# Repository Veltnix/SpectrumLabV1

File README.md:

<h1 align="center">SpectrumLab V1</h1>

<p align="center">
<b>A Compact VIS–NIR Spectroscopy Development Board powered by ESP32-C3 and AS7263</b>
</p>

<hr>

<h2>📌 Overview</h2>

<p>
<b>SpectrumLab V1</b> is a compact VIS–NIR spectroscopy development board built around the ESP32-C3 and the AMS AS7263 spectral sensor.
</p>

<p>
Most spectrometers are big lab instruments. I wanted to see how small and practical a spectral sensing system could be if everything was integrated onto a single embedded board.
</p>

<p>
This project is my attempt to make near-infrared sensing more accessible, portable, and easier to experiment with (and honestly, just more fun to build!) (•‿•)
</p>

<ul>
<li>Compact form factor</li>
<li>USB powered</li>
<li>No moving optics</li>
<li>Wireless capable</li>
<li>Built for experimentation</li>
</ul>

<hr>

<h2>❓ Why I Built This</h2>

<p>
Traditional NIR spectrometers rely on diffraction gratings and mechanical scanning. They are precise, but they are also expensive and not exactly friendly for embedded projects.
</p>

<p>
I wanted something that:
</p>

<ul>
<li>Fits in your hand</li>
<li>Has no moving parts</li>
<li>Can stream data over WiFi</li>
<li>Is easy to integrate into custom hardware projects</li>
</ul>

<p>
SpectrumLab is meant to be both a learning platform and a base for portable sensing ideas such as fruit analysis, material comparison, and reflectance experiments.
</p>

<hr>

<h2>🧠 What This Board Actually Does</h2>

<p>
SpectrumLab measures reflected light intensity at specific wavelengths in the visible to near-infrared range.
</p>

<h3>Main Components</h3>

<ul>
<li><b>ESP32-C3-WROOM-2</b> — Handles processing, USB communication, WiFi and BLE</li>
<li><b>AMS AS7263</b> — 6-channel VIS–NIR spectral sensor</li>
<li><b>128×64 I2C OLED</b> — Displays live spectral data</li>
</ul>

<h3>Spectral Channels</h3>

<ul>
<li>610 nm</li>
<li>680 nm</li>
<li>730 nm</li>
<li>760 nm</li>
<li>810 nm</li>
<li>860 nm</li>
</ul>

<p>
Each channel has about 20 nm bandwidth (FWHM). This does not give a continuous spectrum, but it provides discrete calibrated intensity points that are very useful for classification and trend analysis.
</p>

<h3>How It Measures</h3>

<ol>
<li>The sample is illuminated.</li>
<li>Reflected light enters the AS7263.</li>
<li>The sensor outputs calibrated intensity values.</li>
<li>The ESP32 processes, displays, or streams the data.</li>
</ol>

<p>
Simple, solid-state, and no mechanical scanning (￣▽￣)b
</p>

<hr>

<h2>🔬 What “Compact NIR Spectrometry” Means Here</h2>

<p>
Instead of using a diffraction grating and scanning optics, this board uses a filter-based solid-state spectral sensor.
</p>

<p>
The AS7263 integrates:
</p>

<ul>
<li>Optical filters</li>
<li>On-chip ADC</li>
<li>Digitally calibrated outputs</li>
</ul>

<p>
Because of that, the system:
</p>

<ul>
<li>Has no moving parts</li>
<li>Is physically small</li>
<li>Consumes less power</li>
<li>Is much easier to embed into custom hardware</li>
</ul>

<p>
It is not a lab-grade continuous spectrometer. It is a compact, embedded-friendly spectral measurement platform designed for experimentation and real-world integration.
</p>

<hr>

<h2>🧩 PCB</h2>

<p>
Design goals:
</p>

<ul>
<li>2-layer compact PCB</li>
<li>Fully surface-mount</li>
<li>USB-C powered (5V to 3.3V regulation)</li>
<li>Dedicated I2C breakout pins</li>
<li>Debug jumper bridges</li>
</ul>

<hr>

<h2>📐 Schematics</h2>

<hr>

<h2>💻 Example Code (SSD1306 Interface)</h2>

<pre><code>
#include &lt;Wire.h&gt;
#include &lt;Adafruit_SSD1306.h&gt;
#include "AS726X.h"

#define SDA_PIN 8
#define SCL_PIN 9

#define SCREEN_WIDTH 128
#define SCREEN_HEIGHT 64

Adafruit_SSD1306 display(SCREEN_WIDTH, SCREEN_HEIGHT, &Wire, -1);
AS726X sensor;

void setup() {
  Serial.begin(115200);
  Wire.begin(SDA_PIN, SCL_PIN);

  if (!display.begin(SSD1306_SWITCHCAPVCC, 0x3C)) {
    while (1);
  }

  if (!sensor.begin()) {
    while (1);
  }

  sensor.setGain(AS726X_GAIN_16X);
  sensor.setIntegrationTime(50);
  sensor.enableBulb(AS726X_LED_IR);
}

void loop() {
  sensor.takeMeasurements();
  delay(500);
}
</code></pre>

<hr>

<h2>⭐ Notable Features</h2>

<ul>
<li>ESP32-C3-WROOM-2 with WiFi and BLE</li>
<li>610 nm to 860 nm spectral coverage</li>
<li>~20 nm channel bandwidth</li>
<li>USB-C connectivity</li>
<li>External I2C header</li>
<li>Compact and portable</li>
</ul>

<hr>

<h2>💰 BOM & Manufacturing</h2>

<hr>

<h2>🚀 Potential Applications</h2>

<ul>
<li>Fruit ripeness estimation</li>
<li>Material comparison</li>
<li>Reflectance experiments</li>
<li>Educational spectroscopy demos</li>
<li>Embedded ML classification</li>
</ul>

<hr>

<h2>🛠 Programs Used</h2>

<ul>
<li>KiCad (Schematics & PCB)</li>
<li>Fusion 360 (STEP modeling)</li>
<li>Blender (3D render)</li>
</ul>

<hr>

<h2>🛡 License</h2>

<p>MIT License</p>

<hr>

<h2>❤️ Support</h2>

<p>
Support this project on Hack Club:<br>
<a href="https://blueprint.hackclub.com/projects/12271">
https://blueprint.hackclub.com/projects/12271
</a>
</p>

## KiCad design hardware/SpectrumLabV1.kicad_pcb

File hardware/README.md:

## SpectrumLab V1

## JUMPER
JP1 ... VBUS = 5V jumper (Default: not connected): Connecting this disables the protective SBD between USB and external power supply. To eliminate the voltage drop due to SBD and output the voltage input from USB as it is to 5V, connect this jumper. Note that shorting this pin will increase current consumption by about 0.1mA due to the pull-down resistor on the CC pin.

JP2 ... 5V -> 3.3V jumper (Default: connected): Connection of the external power supply terminal (5V pin) to the power input terminal to the ESP32-C3. Disconnect when suppressing regulator quiescent current.

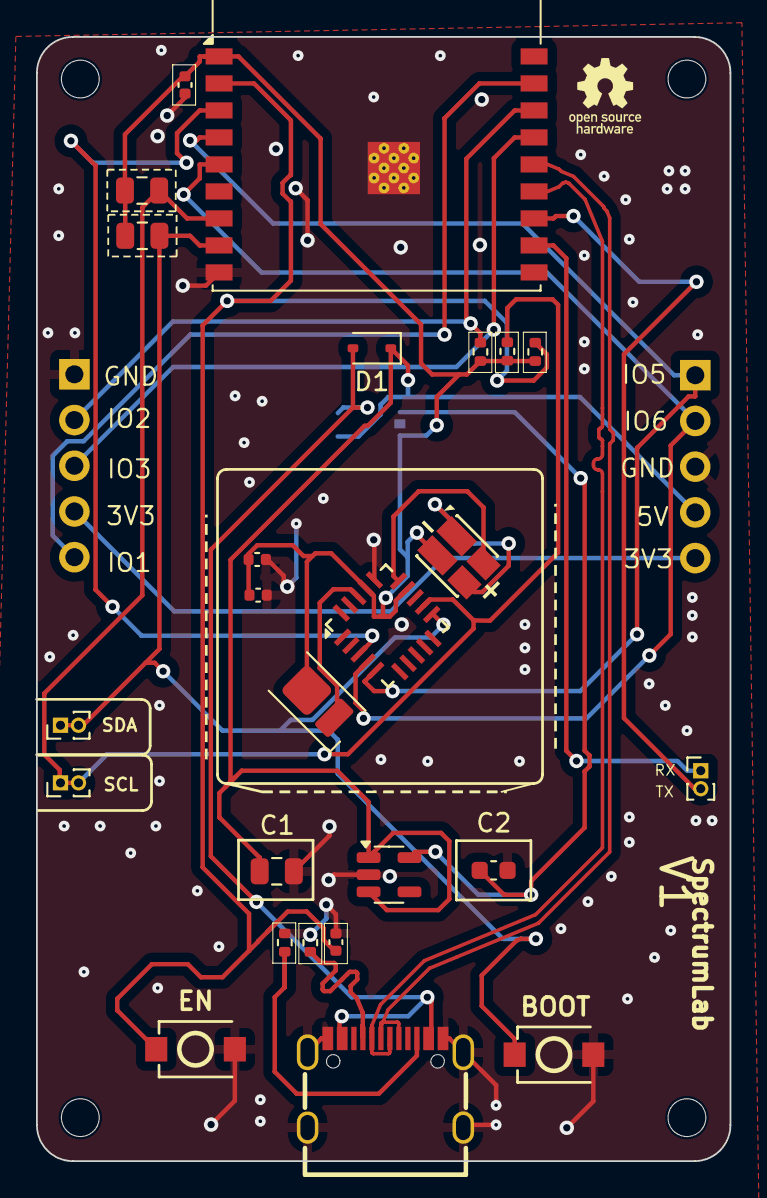
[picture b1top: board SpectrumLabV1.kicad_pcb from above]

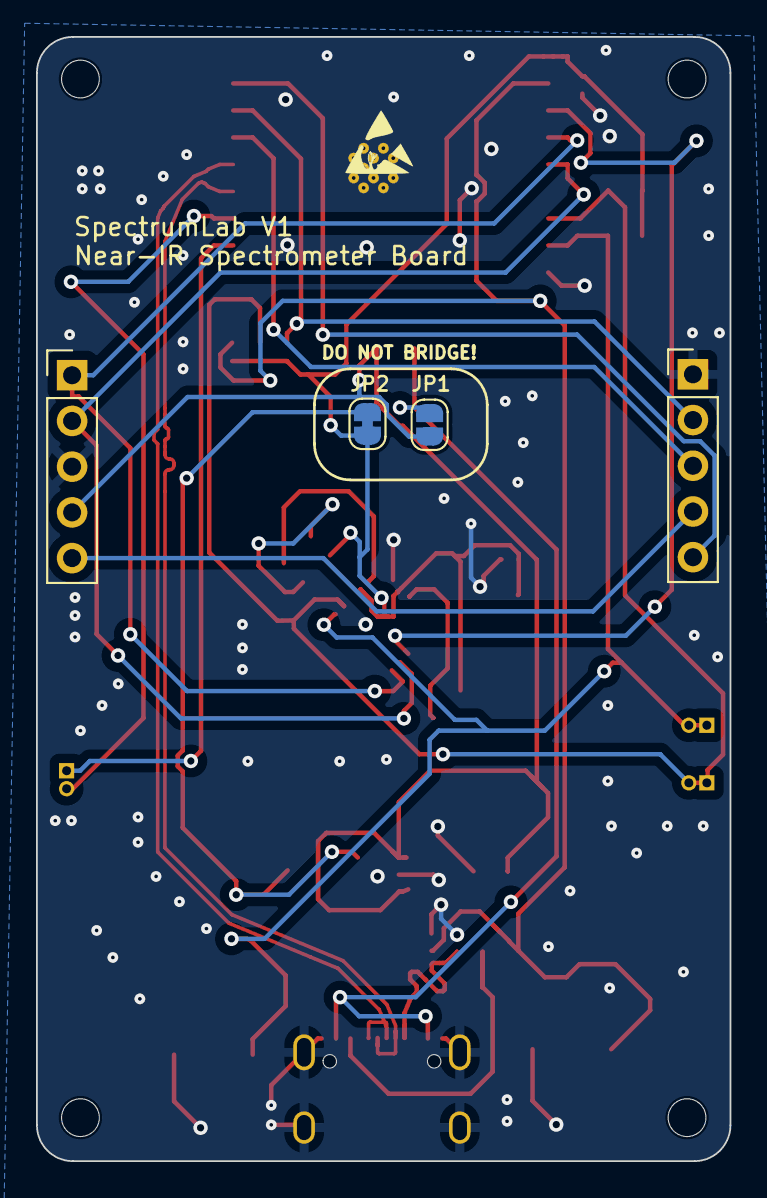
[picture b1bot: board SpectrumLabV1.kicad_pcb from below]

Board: 2 copper layers, 38.5 x 62.5 mm, 29 parts (4 on the bottom side), 24 nets.

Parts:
BOOT1: SW_Push; TS-1088-AR02016
C1: 10u; C_0805_2012Metric
C2: 22u; C_0603_1608Metric
C3: 1u; C_0402_1005Metric
C4, C5: 100n; C_0402_1005Metric
C6: 10uF; C_0402_1005Metric
D1: 1N5819WS; D_SOD-323
D3: LED; LED_Everlight-SMD3528_3.5x2.8mm_67-21ST
D5: LED-SMD_4P-L3.2-W3.0_RS6694-S820B1
EN1: SW_Push; TS-1088-AR02016
J1: USB_C_Receptacle_USB2.0_16P; USB-C_SMD-TYPE-C-31-M-12 (JLC)
J2, J3: Conn_01x05_Pin; PinHeader_1x05_P2.54mm_Vertical
J4, J5, J6: Conn_01x02_Pin; PinHeader_1x02_P1.00mm_Vertical
JP1: SolderJumper_2_Open; SolderJumper-2_P1.3mm_Open_RoundedPad1.0x1.5mm
JP2: SolderJumper_2_Bridged; SolderJumper-2_P1.3mm_Bridged_RoundedPad1.0x1.5mm
R1, R2: 5.1k; R_0402_1005Metric
R3, R4, R5: 10k; R_0402_1005Metric
R6, R7: 2K; C_0805_2012Metric
U1: ESP32-C3-WROOM-02
U2: AS7263; AMS_LGA-20_4.7x4.5mm_P0.65mm
U3: RT9080-33GJ5; SOT-23-5

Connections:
+3V3: C4.2, C5.2, C6.2, D3.2 (A), D5.2, JP2.2 (B), R3.1, R4.1, R5.1, R6.1, R7.1, U1.1 (3V3), U2.14 (VDD), U2.17 (VDD)
+5V: C1.2, D1.1 (K), J3.4, JP1.2 (B), U3.1 (IN), U3.3 (EN)
/3V3: J2.4, J3.5
/EN: C3.1, EN1.1, R5.2, U1.2 (EN/CHIP_PU)
/IO1: J2.5, U1.17 (GPIO1/ADC1_CH1/XTAL_32K_N)
/IO2: J2.2, R3.2, U1.16 (GPIO2/ADC1_CH2)
/IO3: J2.3, U1.15 (GPIO3/ADC1_CH3)
/IO4: U1.3 (GPIO4/ADC1_CH4), U2.3 (SCK)
/IO5: J3.1, U1.4 (GPIO5/ADC2_CH0), U2.5 (MISO)
/IO6: J3.2, U1.5 (GPIO6), U2.4 (MOSI)
/IO18: J1.A7 (D-), J1.B7 (D-), U1.13 (GPIO18/USB_D-)
/IO19: J1.A6 (D+), J1.B6 (D+), U1.14 (GPIO19/USB_D+)
/RXD: J6.1, U1.11 (GPIO20/U0RXD)
/TXD: J6.2, U1.12 (GPIO21/U0TXD)
GND: BOOT1.2, C1.1, C2.2, C3.2, C4.1, C5.1, C6.1, EN1.2, J1.A1 (GND), J1.A12 (GND), J1.B1 (GND), J1.B12 (GND), J1.S1 (SHIELD), J2.1, J3.3, R1.2, R2.1, U1.9 (GND), U1.19 (GND), U2.16 (GND), U3.2 (GND)
unnamed: D3.1 (K), U2.18 (LED_IND)
unnamed: D5.1, D5.4
unnamed: J1.A5 (CC1), R1.1
unnamed: J1.B5 (CC2), R2.2
unnamed: C2.1, JP2.1 (A), U3.5 (OUT)
unnamed: D5.3, U2.15 (LED_DRV)
SCL: J5.1, J5.2, R4.2, R6.2, U1.7 (GPIO8), U2.12 (TX/SDA_S)
SDA: BOOT1.1, J4.1, J4.2, R7.2, U1.8 (GPIO9), U2.11 (RX/SCL_S)
VBUS: D1.2 (A), J1.A4 (VBUS), J1.A9 (VBUS), J1.B4 (VBUS), J1.B9 (VBUS), JP1.1 (A)

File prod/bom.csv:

Comment,Designator,Footprint,JLCPCB Part #
2K,"R6,R7",0805,C17604
10u,C1,0805,C15850
,D5,LED-SMD_4P-L3.2-W3.0_RS6694-S820B1,C19944431
ESP32-C3-WROOM-02,U1,ESP32-C3-WROOM-02,C2934560
1u,C3,0402,C52923
AS7263,U2,AMS_LGA-20_4.7x4.5mm_P0.65mm,C2655137
1N5819WS,D1,D_SOD-323,C191023
5.1k,"R1,R2",0402,C25905
USB_C_Receptacle_USB2.0_16P,J1,USB-C_SMD-TYPE-C-31-M-12(JLC),C2988369
10k,"R3,R4,R5",0402,C25744
22u,C2,0603,C59461
100n,"C6,C4,C5,C6,C4,C5",0402,C1525
LED,D3,LED_Everlight-SMD3528_3.5x2.8mm_67-21ST,C2830527
SW_Push,"BOOT1,EN1",TS-1088-AR02016,C720477
RT9080-33GJ5,U3,SOT-23-5,C841192

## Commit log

2026-02-21 Add production files
2026-02-21 Add netlist data for components and connections
    Added netlist data for various components and connections.
2026-02-22 Replaced Prod File with the corrected BOM and Footprint
2026-02-22 Add Media & Hardware
2026-02-22 Add MIT License to the project
2026-02-22 Update README with updated schematcs image
2026-02-22 Add support section to README
2026-02-22 Updated bom.csv on prod
2026-02-22 Added media
2026-02-22 Align PCB image in README
    Align PCB image to the left in README.
2026-02-22 Update README with images and PCB details
    Added images and updated PCB section in README.
2026-02-22 Adjust image dimensions in README.md
    Updated image size for better layout in README.
2026-02-28 Fix header formatting in README.md
2026-02-28 Update example code section header in README
2026-03-05 Revise README for SpectrumLab V1 with detailed features
    Updated README.md to enhance project description and features.
